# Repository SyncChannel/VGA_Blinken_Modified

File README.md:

# VGA Blinken with Onboard Connector
Modified version of the VGA Blinking Lights PBC by Danjovic:<br>
https://github.com/Danjovic/VGA_Blinken<br>
https://hackaday.io/project/8537-vga-blinking-lights<br>

This version of the PCB has SMD passives to save space, but adds an onboard DB-15 connector for easy connection to a monitor. The PIC microcontroller is still DIP and socketed to allow for external programming.

See the original project page for the parts values, firmware, etc. The passives are 0603. The DB-15 footprint is for a standard through-hole, right angle connector (Amphenol FCI ICD15S13E6GV00LF or similar).<br>

It’s no longer 1" square, but it’s a lot easier to hook up that monitor with the onboard connector!<br>

Order PCBs on OSH Park:<br>
https://oshpark.com/shared_projects/7fWiMppm<br>

Original version of the PCB on OSH Park:<br>
https://oshpark.com/shared_projects/BGKXsEzu<br>

All credit goes to Danjovic, the original creator. This is an awesome project.

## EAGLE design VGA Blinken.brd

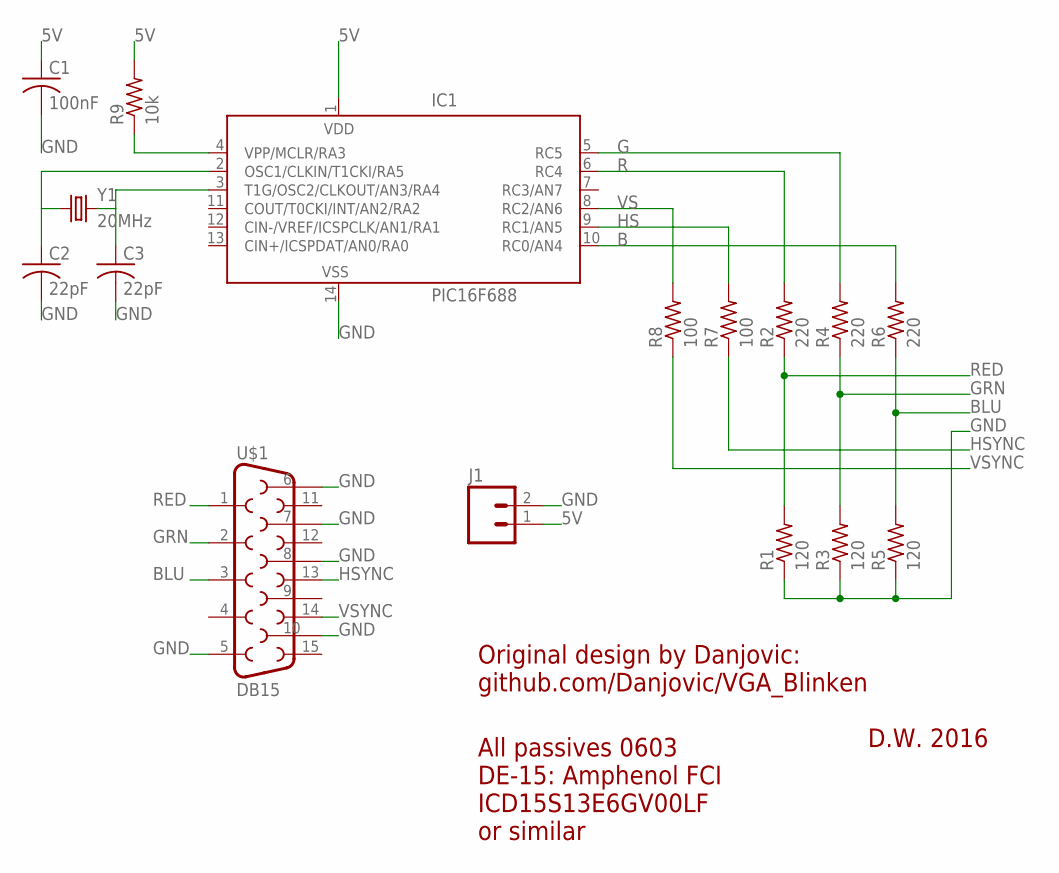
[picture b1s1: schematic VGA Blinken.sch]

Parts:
C1: 100nF; C0603
C2, C3: 22pF; C0603
IC1: PIC16F688; DIL14
J1: M02PTH; 1X02
R1, R3, R5: 120; R0603
R2, R4, R6: 220; R0603
R7, R8: 100; R0603
R9: 10k; R0603
U$1: DB15
Y1: 20MHz; HC49U-V

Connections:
5V: C1.1, IC1.1 (VDD), J1.1, R9.2
B: IC1.10 (RC0/AN4), R6.2
BLU: R5.2, R6.1, U$1.3
G: IC1.5 (RC5), R4.2
GND: C1.2, C2.2, C3.2, IC1.14 (VSS), J1.2, R1.1, R3.1, R5.1, U$1.5, U$1.6, U$1.7, U$1.8, U$1.10
GRN: R3.2, R4.1, U$1.2
HS: IC1.9 (RC1/AN5), R7.2
HSYNC: R7.1, U$1.13
R: IC1.6 (RC4), R2.2
RED: R1.2, R2.1, U$1.1
RST: IC1.4 (VPP/MCLR/RA3), R9.1
VS: IC1.8 (RC2/AN6), R8.2
VSYNC: R8.1, U$1.14
X1: C2.1, IC1.2 (OSC1/CLKIN/T1CKI/RA5), Y1.1
X2: C3.1, IC1.3 (T1G/OSC2/CLKOUT/AN3/RA4), Y1.2

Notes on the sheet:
Original design by Danjovic: github.com/Danjovic/VGA_Blinken
D.W. 2016
All passives 0603 DE-15: Amphenol FCI ICD15S13E6GV00LF or similar

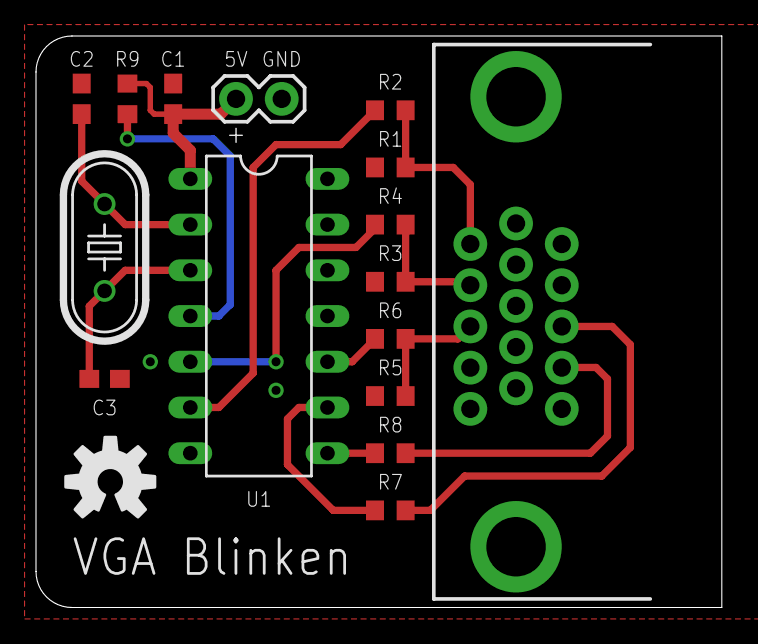
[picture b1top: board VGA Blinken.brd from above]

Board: 2 copper layers, 38.1 x 31.8 mm, 17 parts (0 on the bottom side), 15 nets.

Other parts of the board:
U$2: OSHW-LOGO-M

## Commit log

2016-12-31 :circus_tent: Added .gitattributes & .gitignore files
2016-12-31 Added Eagle Files
2016-12-31 Created folder for Eagle Files

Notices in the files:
parts and their libraries:
SparkFun-FreqCtrl: Licensing: Creative Commons ShareAlike 4.0 International - https://creativecommons.org/licenses/by-sa/4.0
